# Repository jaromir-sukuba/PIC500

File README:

AVR ISP programmer, implemented in PIC16F1825. Based on http://www.tuxgraphics.org/electronics/200510/article05101.shtml
More info at http://jaromir.xf.cz/avr/pic500.html

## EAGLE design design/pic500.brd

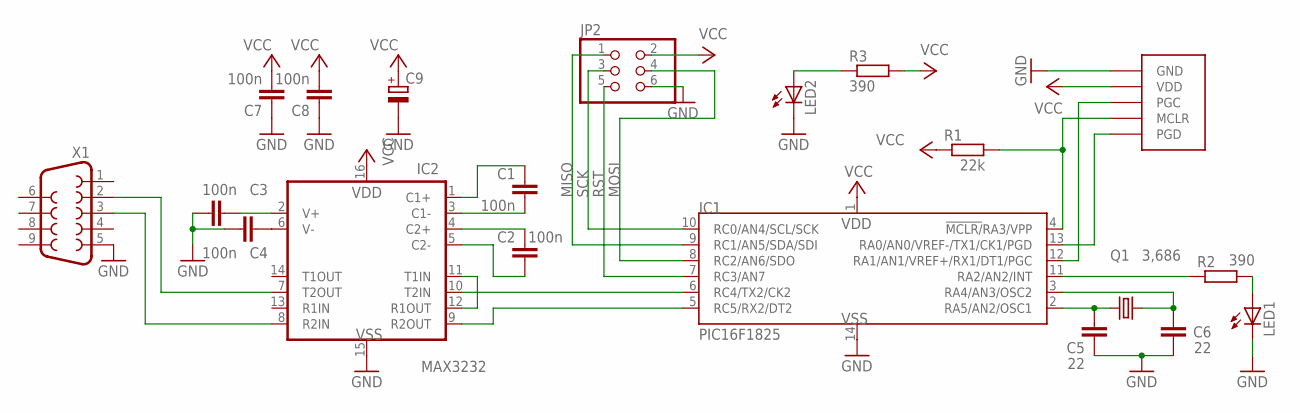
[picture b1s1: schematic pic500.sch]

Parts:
C1, C2, C3, C4, C7, C8: 100n; C025-025X050
C5, C6: 22; C025-025X050
C9: CPOL-EUE2-5; E2-5
IC1: PIC16F1825; DIL14
IC2: MAX3232; DIL16
JP2: PINHD-2X03_2.54; 2X03
LED1, LED2: LED3MM
Q1: 3,686; HC49/S
R1: 22k; 0207/10
R2, R3: 390; 0207/10
U$1: PROGHEAD_254
X1: F09HP

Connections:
GND: C3.2, C4.2, C5.1, C6.1, C7.1, C8.1, C9.-, IC1.14 (VSS), IC2.15 (VSS), JP2.6, LED1.K (C), LED2.K (C), U$1.GND, X1.5
MISO: IC1.9 (RC1/AN5/SDA/SDI), JP2.1
MOSI: IC1.8 (RC2/AN6/SDO), JP2.4
unnamed: IC1.5 (RC5/RX2/DT2), IC2.9 (R2OUT)
unnamed: IC1.6 (RC4/TX2/CK2), IC2.10 (T2IN)
unnamed: IC2.11 (T1IN), IC2.12 (R1OUT)
unnamed: IC2.7 (T2OUT), X1.2
unnamed: IC2.8 (R2IN), X1.3
unnamed: C2.2, IC2.5 (C2-)
unnamed: C2.1, IC2.4 (C2+)
unnamed: C1.2, IC2.3 (C1-)
unnamed: C1.1, IC2.1 (C1+)
unnamed: C3.1, IC2.2 (V+)
unnamed: C4.1, IC2.6 (V-)
unnamed: C5.2, IC1.2 (RA5/AN2/OSC1), Q1.1
unnamed: C6.2, IC1.3 (RA4/AN3/OSC2), Q1.2
unnamed: LED2.A, R3.1
unnamed: IC1.13 (RA0/AN0/VREF-/TX1/CK1/PGD), U$1.PGD
unnamed: IC1.12 (RA1/AN1/VREF+/RX1/DT1/PGC), U$1.PGC
unnamed: IC1.4 (!MCLR/!RA3/VPP), R1.2, U$1.MCLR
unnamed: IC1.11 (RA2/AN2/INT), R2.1
unnamed: LED1.A, R2.2
RST: IC1.7 (RC3/AN7), JP2.5
SCK: IC1.10 (RC0/AN4/SCL/SCK), JP2.3
VCC: C7.2, C8.2, C9.+, IC1.1 (VDD), IC2.16 (VDD), JP2.2, R1.1, R3.2, U$1.VDD

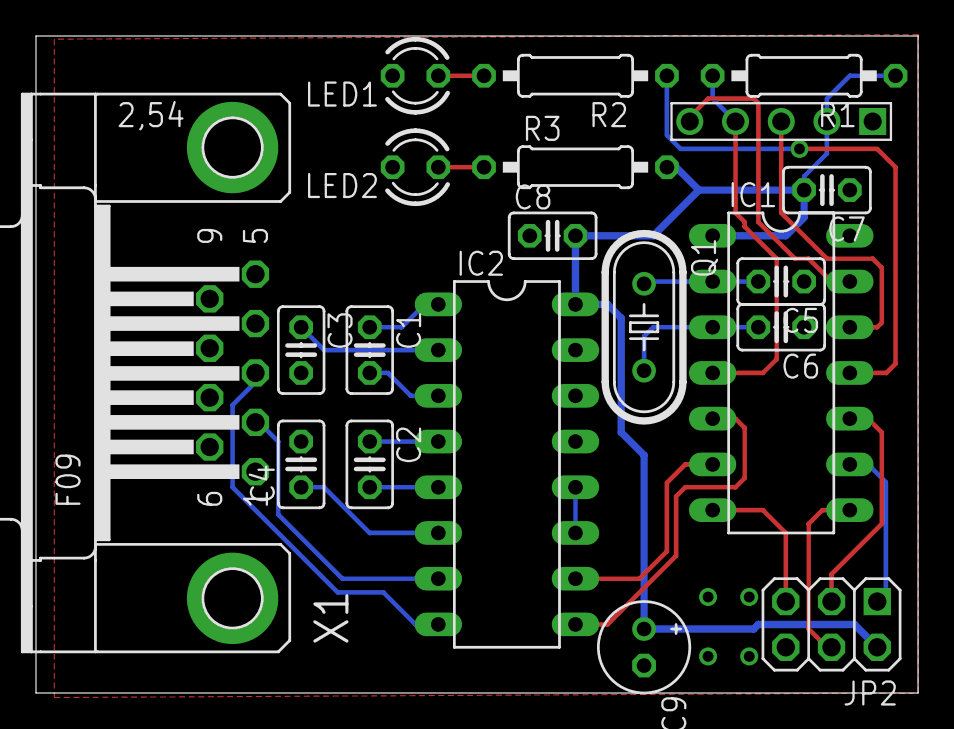
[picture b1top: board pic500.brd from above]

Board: 2 copper layers, 49.0 x 36.5 mm, 20 parts (0 on the bottom side), 25 nets.

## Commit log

2014-03-18 ver 1
    initial release
2014-03-19 schem v 1
2014-03-19 design files 1
